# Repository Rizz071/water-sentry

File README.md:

# WaterSentry 🌊🏹

**WaterSentry** — это полностью автономная система дальнего беспроводного мониторинга уровня жидкости и предотвращения затоплений. 

Проект разработан для условий, где **абсолютно недоступны или ненадежны классические каналы связи**: нет Wi-Fi, интернета, сотовых сетей (GSM) и абонентской платы. Связь между удаленным датчиком и базовой станцией осуществляется напрямую по радиоканалу LoRa.

---

## 💡 Как это работает

1. **Удаленный датчик** устанавливается в месте возможного разлива (подвал, колодец, резервуар, насосная). Раз в 5 минут он отправляет короткий сигнал «я жив» (*heartbeat*).
2. **В случае перелива** датчик мгновенно выходит из режима ожидания и отправляет внеочередной пакет с флагом аварии.
3. **Базовая станция**, находящаяся на значительном удалении (в доме, диспетчерской), принимает сигнал, включает световую индикацию тревоги и запускает мощную сирену (зуммер) для привлечения внимания человека.

---

## 🚀 Ключевые особенности

* **Независимость от инфраструктуры:** Никаких сим-карт, роутеров и облачных сервисов. Прямая связь «точка-точка».
* **Огромная дальность:** Благодаря модулям LoRa на частоте 433 МГц сигнал уверенно пробивает железобетонные перекрытия, стены и распространяется на большие расстояния в условиях сложного рельефа.
* **Экстремальный минимализм протокола:** Данные упакованы в компактную структуру размером всего **6 байт**. Это минимизирует время работы передатчика в эфире (*Time on Air*), повышает пробивную способность радиосигнала и экономит энергию.
* **Промышленная надежность:** Код написан на **чистом Си** под нативный фреймворк **ESP-IDF v5.x**.
* **Гибкая отладка

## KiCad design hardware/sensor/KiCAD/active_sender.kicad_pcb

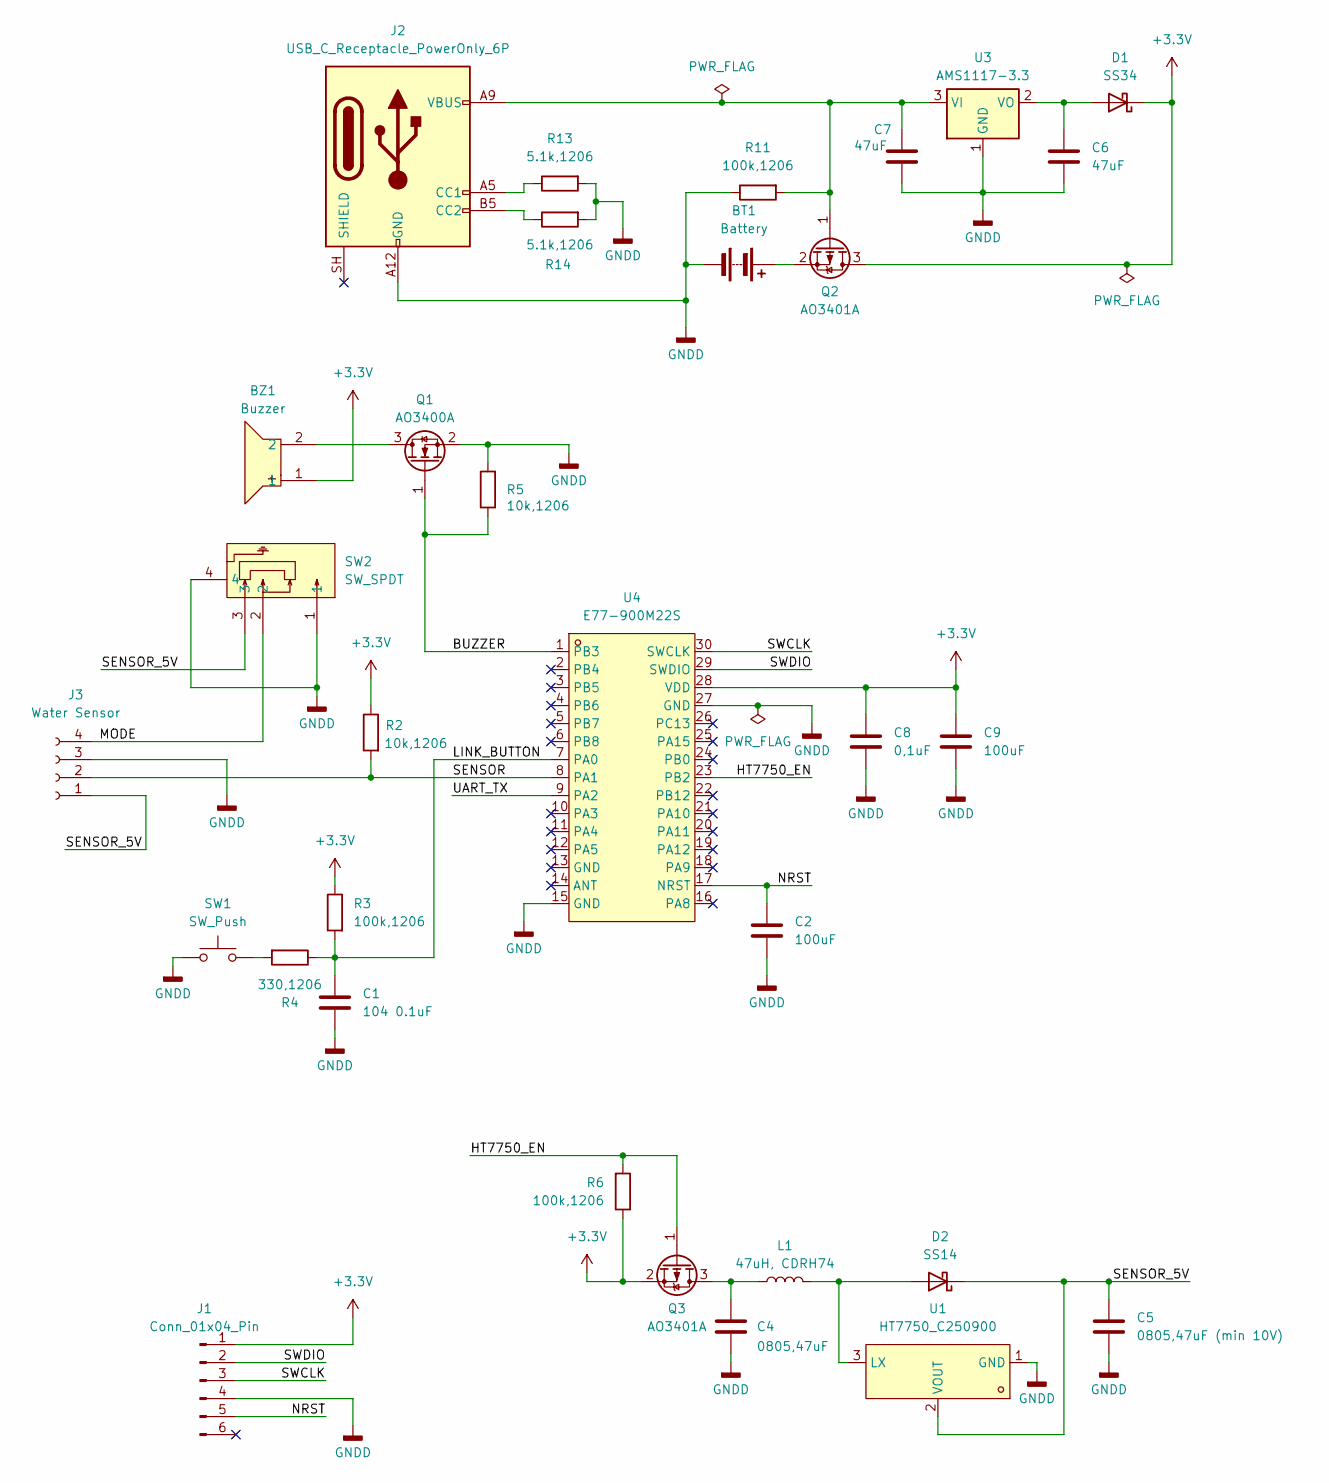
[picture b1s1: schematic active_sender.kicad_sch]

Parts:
BT1: Battery; CR123A-SMD_BH-123A-B5BA003
BZ1: Buzzer; Huaneng MLT-9650; MPN MLT-9650; LCSC Part C96127
C1: 104 0.1uF; C_0805_2012Metric_Pad1.18x1.45mm_HandSolder
C2, C9: 100uF; C_0805_2012Metric_Pad1.18x1.45mm_HandSolder
C4: 0805,47uF; C_0805_2012Metric_Pad1.18x1.45mm_HandSolder
C5: 0805,47uF (min 10V); C_0805_2012Metric_Pad1.18x1.45mm_HandSolder
C6, C7: 47uF; C_0805_2012Metric_Pad1.18x1.45mm_HandSolder
C8: 0,1uF; C_0805_2012Metric_Pad1.18x1.45mm_HandSolder
D1: SS34; D_SMA
D2: SS14; D_SMA
J1: Conn_01x04_Pin; PinHeader_2x03_P2.54mm_Vertical_SMD
J2: USB_C_Receptacle_PowerOnly_6P; USB_C_Receptacle_GCT_USB4125-xx-x-0190_6P_TopMnt_Horizontal
J3: Water Sensor; JST_XH_S4B-XH-SM4-TB_1x04-1MP_P2.50mm_Horizontal
L1: 47uH, CDRH74; L_7.3x7.3_H4.5
Q1: AO3400A; SOT-23
Q2, Q3: AO3401A; SOT-23
R2, R5: 10k,1206; R_1206_3216Metric_Pad1.30x1.75mm_HandSolder
R3, R6, R11: 100k,1206; R_1206_3216Metric_Pad1.30x1.75mm_HandSolder
R4: 330,1206; R_1206_3216Metric_Pad1.30x1.75mm_HandSolder
R13, R14: 5.1k,1206; R_1206_3216Metric_Pad1.30x1.75mm_HandSolder
SW1: SW_Push; SW_Push_1TS009xxxx-xxxx-xxxx_6x6x5mm
SW2: SW_SPDT; MSK12-C02; MPN MSK12C02; LCSC Part C431540
U1: HT7750_C250900; HT7750; MPN HT7750; LCSC Part C250900
U3: AMS1117-3.3; SOT-223-3_TabPin2
U4: E77-900M22S; COMM-SMD_30P-L20.0-W14.0-P1.27; MPN E77-900M22S; LCSC Part C5124422

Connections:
+3.3V: BZ1.1, C8.1, C9.1, D1.1 (K), J1.1, Q2.3 (D), Q3.2 (S), R2.1, R3.1, R6.1, U4.28 (VDD)
/BUZZER: Q1.1 (G), R5.1, U4.1 (PB3)
/HT7750_EN: Q3.1 (G), R6.2, U4.23 (PB2)
/LINK_BUTTON: C1.1, R3.2, R4.1, U4.7 (PA0)
/MODE: J3.4, SW2.2
/NRST: C2.1, J1.5, U4.17 (NRST)
/SENSOR: J3.2, R2.2, U4.8 (PA1)
/SENSOR_5V: C5.1, D2.1 (K), J3.1, SW2.3, U1.2 (VOUT)
/SWCLK: J1.3, U4.30 (SWCLK)
/SWDIO: J1.2, U4.29 (SWDIO)
/UART_TX: U4.9 (PA2)
GNDD: BT1.2 (-), C1.2, C2.2, C4.2, C5.2, C6.2, C7.2, C8.2, C9.2, J1.4, J2.A12 (GND), J2.B12 (GND), J3.3, Q1.2 (S), R5.2, R11.1, R13.2, R14.2, SW1.1, SW2.1, SW2.4, U1.1 (GND), U3.1 (GND), U4.15 (GND), U4.27 (GND)
unnamed: BT1.1 (+), Q2.2 (S)
unnamed: C6.1, D1.2 (A), U3.2 (VO)
unnamed: D2.2 (A), L1.2, U1.3 (LX)
unnamed: J2.A5 (CC1), R13.1
unnamed: J2.B5 (CC2), R14.1
unnamed: BZ1.2, Q1.3 (D)
unnamed: C7.1, J2.A9 (VBUS), J2.B9 (VBUS), Q2.1 (G), R11.2, U3.3 (VI)
unnamed: C4.1, L1.1, Q3.3 (D)
unnamed: R4.2, SW1.2

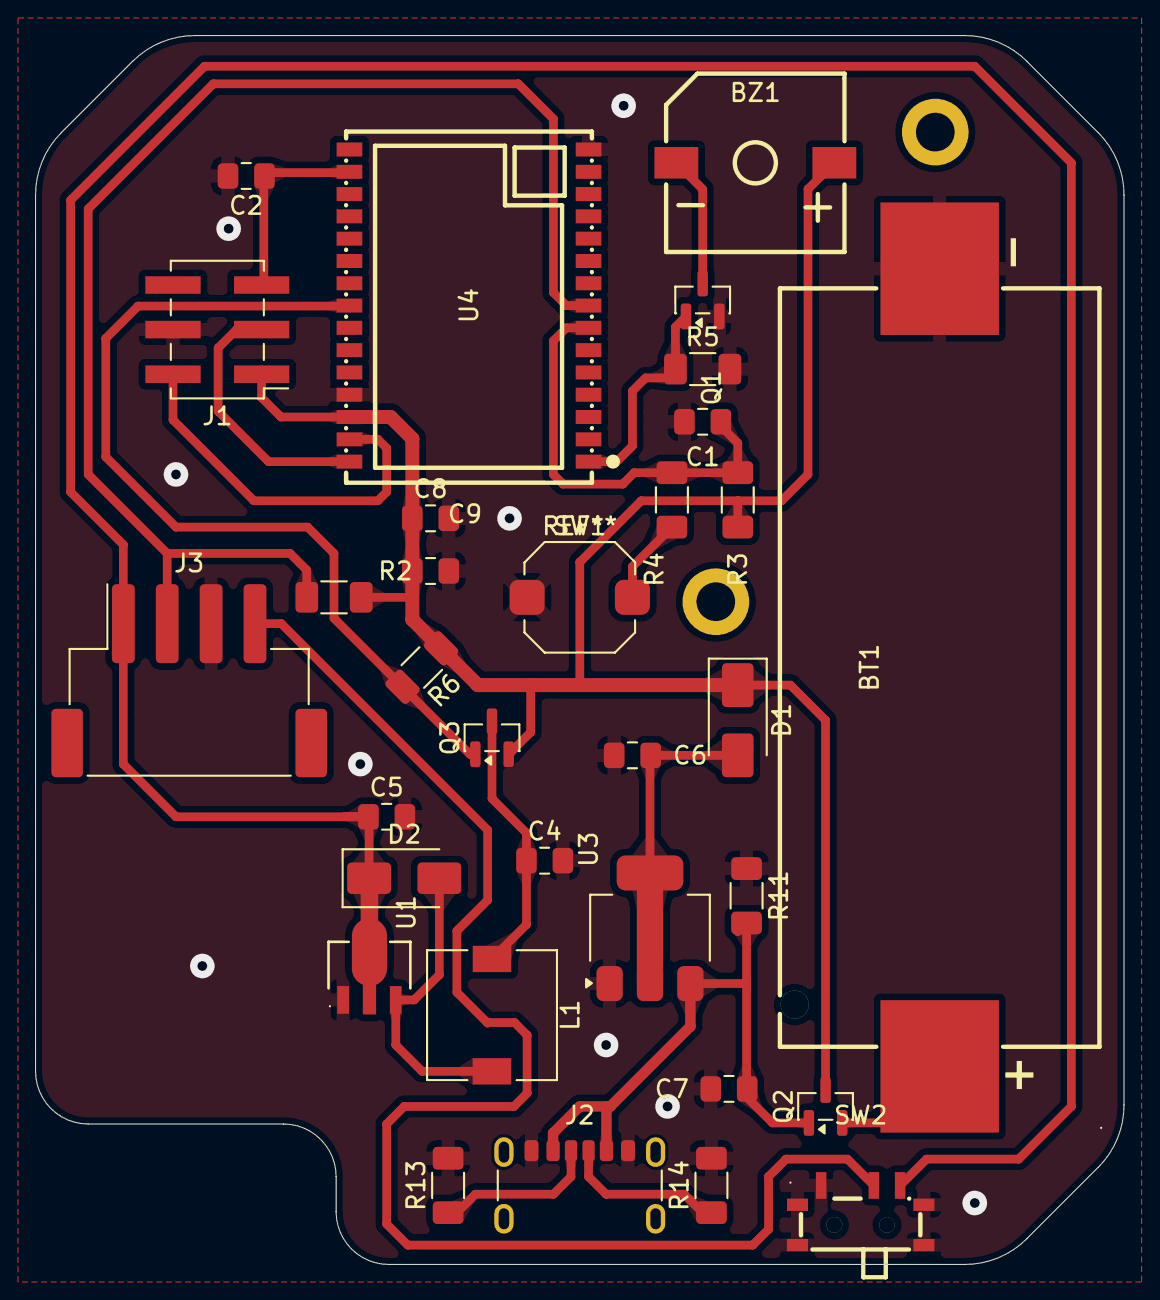
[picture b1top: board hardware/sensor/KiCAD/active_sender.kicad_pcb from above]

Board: 2 copper layers, 62.0 x 70.0 mm, 32 parts (0 on the bottom side), 20 nets.

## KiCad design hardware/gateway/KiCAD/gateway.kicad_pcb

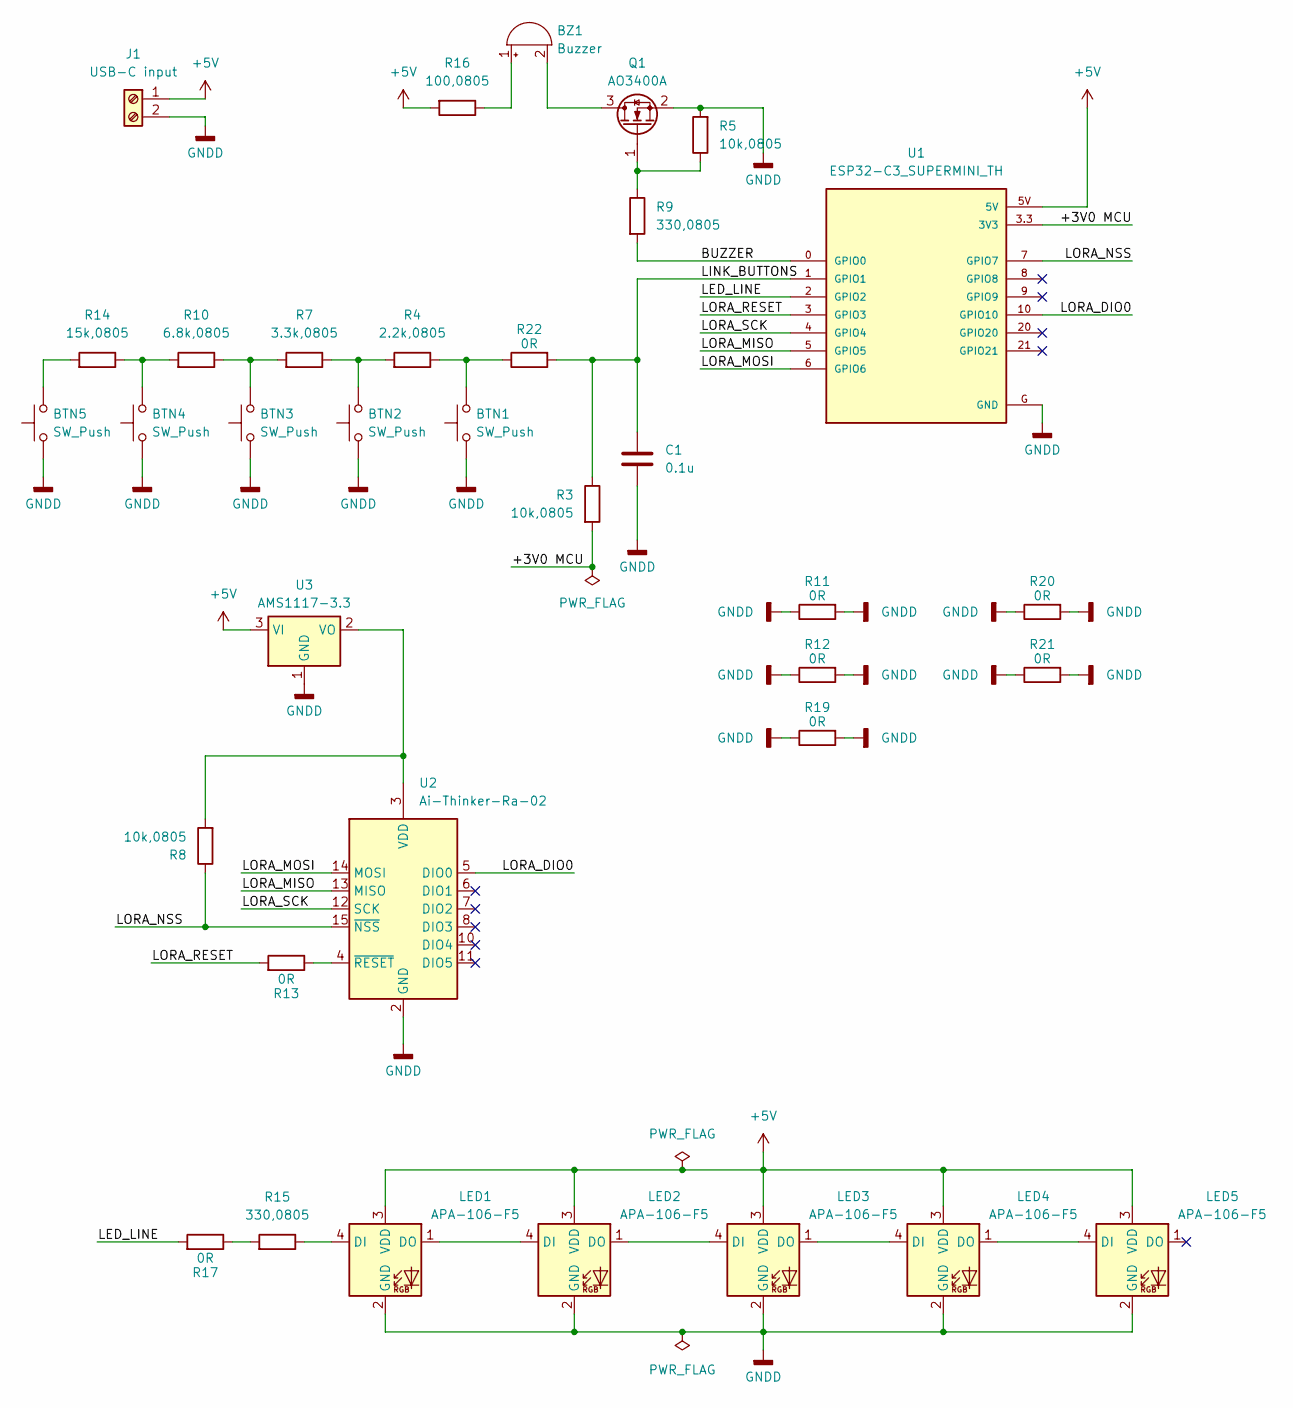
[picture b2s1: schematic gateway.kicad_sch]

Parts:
BTN1, BTN2, BTN3, BTN4, BTN5: SW_Push; SW_PUSH_6mm_H5mm
BZ1: Buzzer; Buzzer_12x9.5RM7.6
C1: 0.1u; C_0805_2012Metric_Pad1.18x1.45mm_HandSolder
J1: USB-C input; TerminalBlock_Phoenix_MKDS-1,5-2_1x02_P5.00mm_Horizontal
LED1, LED2, LED3, LED4, LED5: APA-106-F5; LED_D5.0mm-4_RGB_Staggered_Pins
Q1: AO3400A; SOT-23
R3, R5, R8: 10k,0805; R_0805_2012Metric_Pad1.20x1.40mm_HandSolder
R4: 2.2k,0805; R_0805_2012Metric_Pad1.20x1.40mm_HandSolder
R7: 3.3k,0805; R_0805_2012Metric_Pad1.20x1.40mm_HandSolder
R9, R15: 330,0805; R_0805_2012Metric_Pad1.20x1.40mm_HandSolder
R10: 6.8k,0805; R_0805_2012Metric_Pad1.20x1.40mm_HandSolder
R11, R12, R13, R17, R19, R20, R21, R22: 0R; R_2512_6332Metric_Pad1.40x3.35mm_HandSolder
R14: 15k,0805; R_0805_2012Metric_Pad1.20x1.40mm_HandSolder
R16: 100,0805; R_0805_2012Metric_Pad1.20x1.40mm_HandSolder
U1: ESP32-C3_SUPERMINI_TH; MODULE_ESP32-C3_SUPERMINI_TH
U2: Ai-Thinker-Ra-02; Ai-Thinker-Ra-01-LoRa BREAKOUT BOARD
U3: AMS1117-3.3; SOT-223-3_TabPin2

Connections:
+5V: J1.1, LED1.3 (VDD), LED2.3 (VDD), LED3.3 (VDD), LED4.3 (VDD), LED5.3 (VDD), R16.2, U1.5V, U3.3 (VI)
/+3V0 MCU: R3.2, U1.3.3 (3V3)
/BUZZER: R9.2, U1.0 (GPIO0)
/LED_LINE: R17.2, U1.2 (GPIO2)
/LINK_BUTTONS: C1.1, R3.1, R22.2, U1.1 (GPIO1)
/LORA_DIO0: U1.10 (GPIO10), U2.5 (DIO0)
/LORA_MISO: U1.5 (GPIO5), U2.13 (MISO)
/LORA_MOSI: U1.6 (GPIO6), U2.14 (MOSI)
/LORA_NSS: R8.1, U1.7 (GPIO7), U2.15 (~NSS)
/LORA_RESET: R13.2, U1.3 (GPIO3)
/LORA_SCK: U1.4 (GPIO4), U2.12 (SCK)
GNDD: BTN1.1, BTN2.1, BTN3.1, BTN4.1, BTN5.1, C1.2, J1.2, LED1.2 (GND), LED2.2 (GND), LED3.2 (GND), LED4.2 (GND), LED5.2 (GND), Q1.2 (S), R5.2, R11.1, R11.2, R12.1, R12.2, R19.1, R19.2, R20.1, R20.2, R21.1, R21.2, U1.G (GND), U2.1 (GND), U2.2 (GND), U2.9 (GND), U2.16 (GND), U3.1 (GND)
unnamed: BTN1.2, R4.1, R22.1
unnamed: BTN2.2, R4.2, R7.1
unnamed: BTN3.2, R7.2, R10.1
unnamed: BTN4.2, R10.2, R14.1
unnamed: BTN5.2, R14.2
unnamed: BZ1.1 (+), R16.1
unnamed: BZ1.2 (-), Q1.3 (D)
unnamed: LED1.4 (DI), R15.1
unnamed: LED1.1 (DO), LED2.4 (DI)
unnamed: LED2.1 (DO), LED3.4 (DI)
unnamed: LED3.1 (DO), LED4.4 (DI)
unnamed: LED4.1 (DO), LED5.4 (DI)
unnamed: Q1.1 (G), R5.1, R9.1
unnamed: R15.2, R17.1
unnamed: R8.2, U2.3 (VDD), U3.2 (VO)
unnamed: R13.1, U2.4 (~RESET)

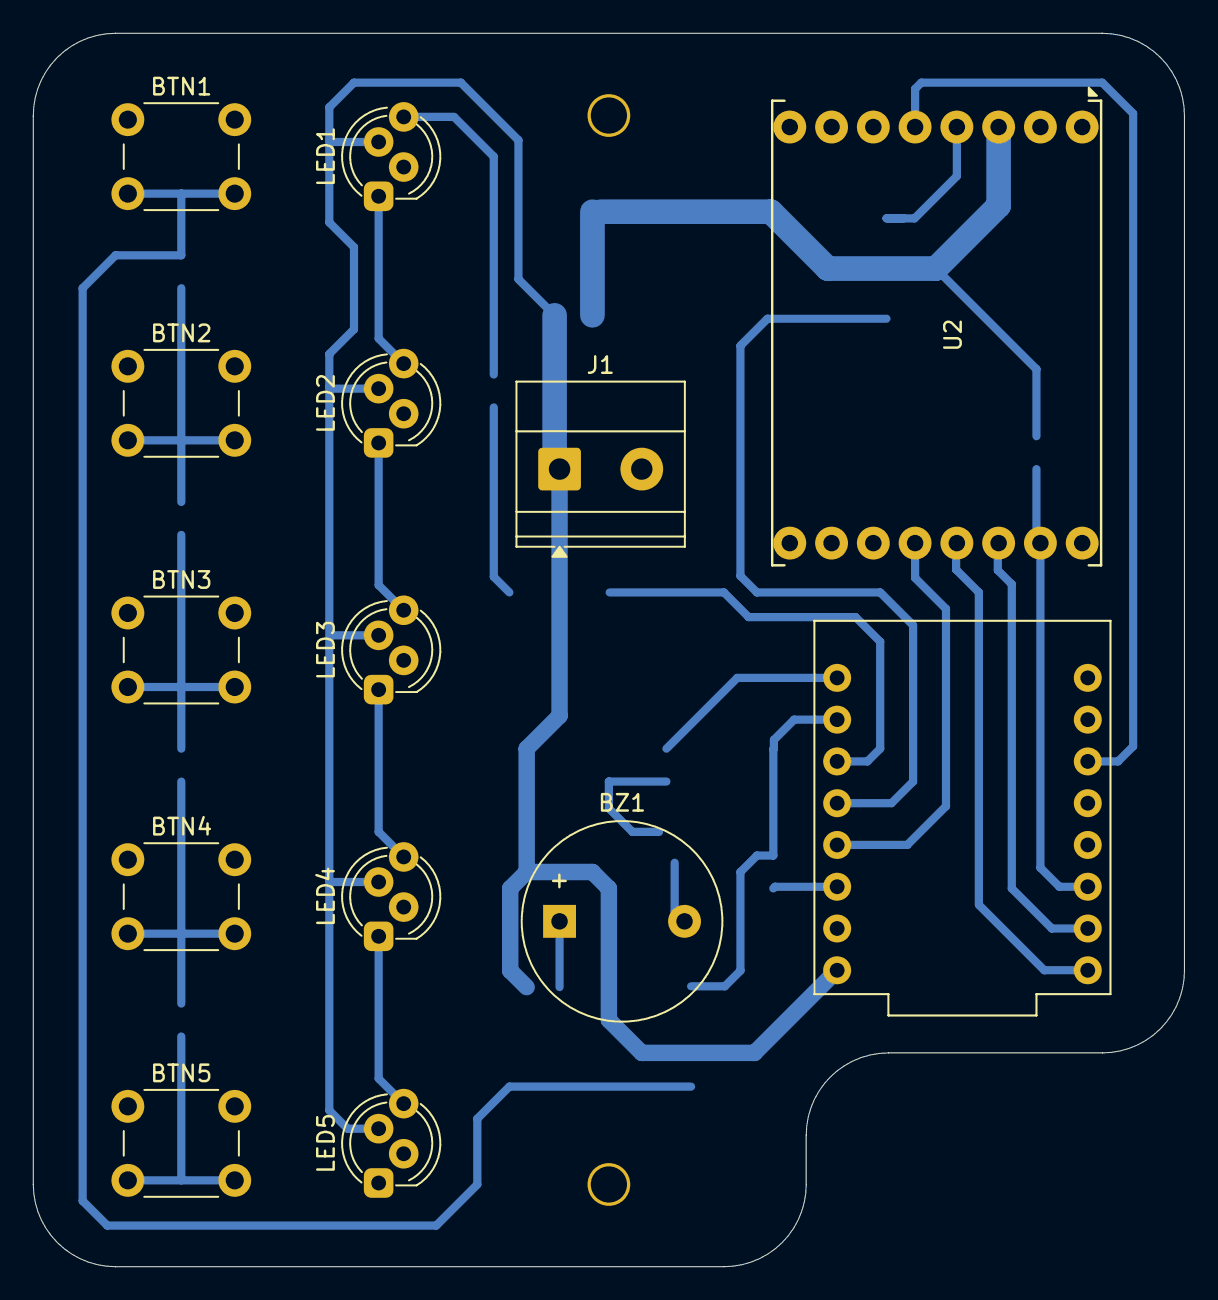
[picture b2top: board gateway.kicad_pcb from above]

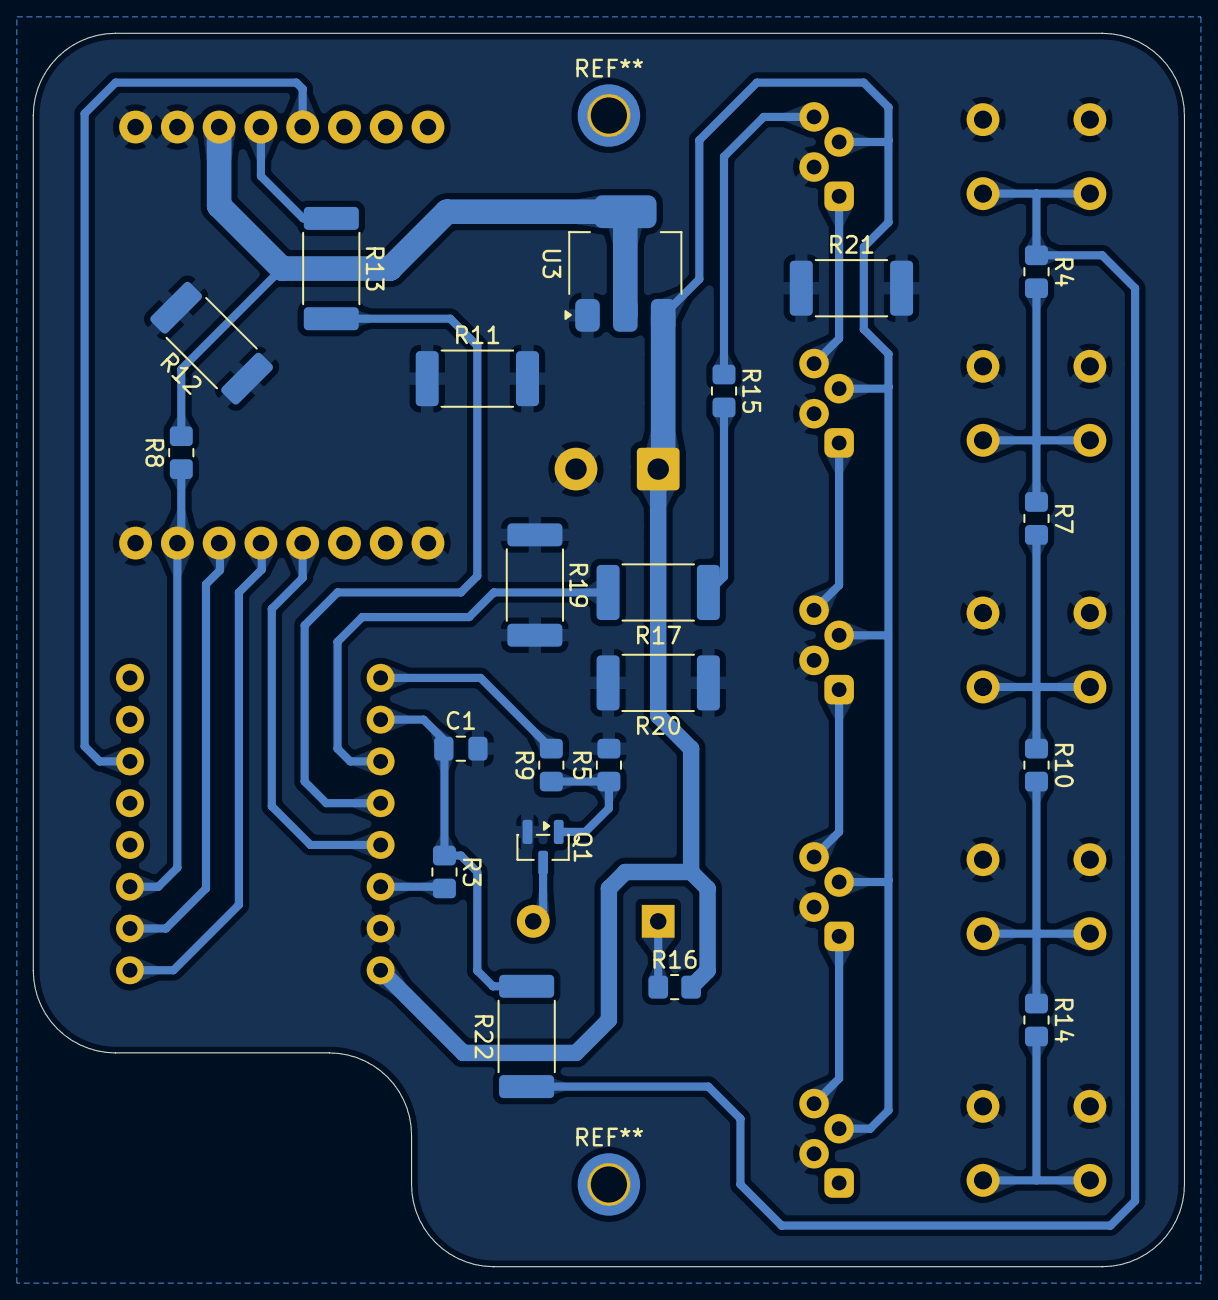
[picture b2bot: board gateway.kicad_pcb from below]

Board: 2 copper layers, 70.0 x 75.0 mm, 35 parts (21 on the bottom side), 28 nets.

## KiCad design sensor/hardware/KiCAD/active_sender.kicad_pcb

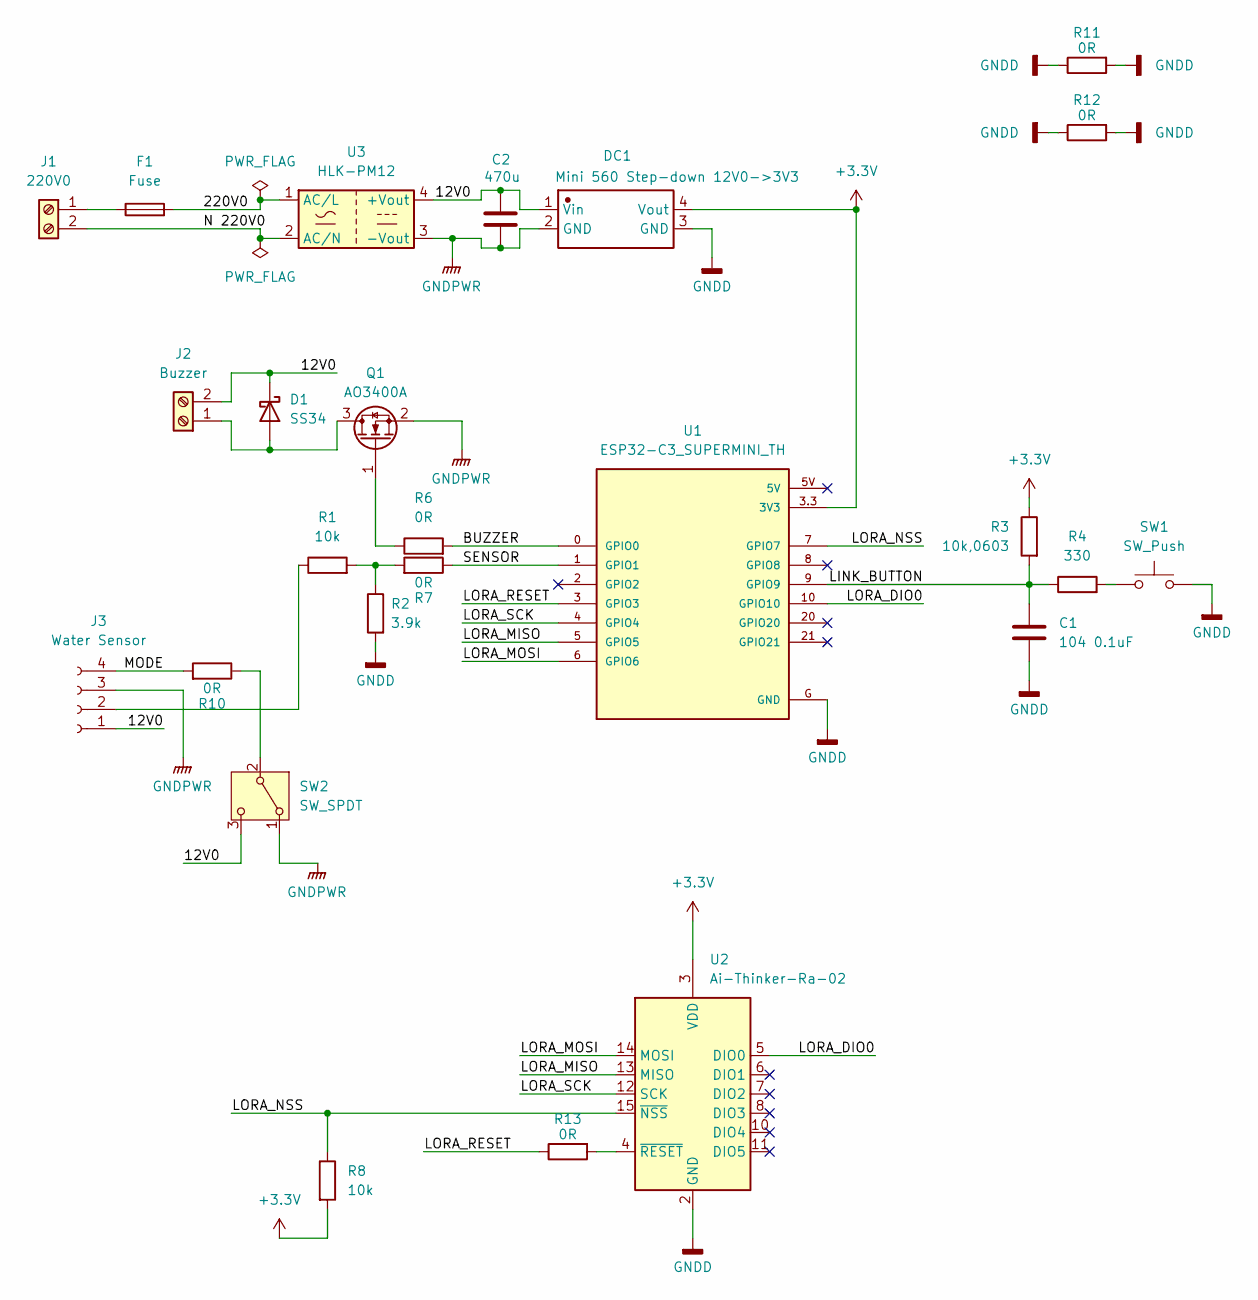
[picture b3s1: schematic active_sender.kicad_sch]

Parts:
C1: 104 0.1uF; C_0805_2012Metric_Pad1.18x1.45mm_HandSolder
C2: 470u; C_Radial_D8.0mm_H11.5mm_P3.50mm
D1: SS34; D_SMA
DC1: Mini 560 Step-down 12V0->3V3; MINI 560 PRO
F1: Fuse; Fuseholder_Cylinder-5x20mm_Schurter_0031_8201_Horizontal_Op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
J1: 220V0; TerminalBlock_Phoenix_MKDS-1,5-2_1x02_P5.00mm_Horizontal
J2: Buzzer; TerminalBlock_Phoenix_MKDS-1,5-2_1x02_P5.00mm_Horizontal
J3: Water Sensor; JST_XH_S4B-XH-A-1_1x04_P2.50mm_Horizontal
Q1: AO3400A; SOT-23
R1, R8: 10k; R_1206_3216Metric_Pad1.30x1.75mm_HandSolder
R2: 3.9k; R_1206_3216Metric_Pad1.30x1.75mm_HandSolder
R3: 10k,0603; R_1206_3216Metric_Pad1.30x1.75mm_HandSolder
R4: 330; R_1206_3216Metric_Pad1.30x1.75mm_HandSolder
R6, R7, R10, R11, R12, R13: 0R; R_2512_6332Metric_Pad1.40x3.35mm_HandSolder
SW1: SW_Push; SW_PUSH_6mm_H5mm
SW2: SW_SPDT; SS12D00
U1: ESP32-C3_SUPERMINI_TH; MODULE_ESP32-C3_SUPERMINI_TH
U2: Ai-Thinker-Ra-02; Ai-Thinker-Ra-01-LoRa BREAKOUT BOARD
U3: HLK-PM12; Converter_ACDC_Hi-Link_HLK-PMxx

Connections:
+3.3V: DC1.4 (Vout), R3.1, R8.2, U1.3.3 (3V3), U2.3 (VDD)
/12V0: C2.1, D1.1 (K), DC1.1 (Vin), J2.2, J3.1, SW2.3 (C), U3.4 (+Vout)
/220V0: F1.2, U3.1 (AC/L)
/BUZZER: R6.2, U1.0 (GPIO0)
/LINK_BUTTON: C1.1, R3.2, R4.1, U1.9 (GPIO9)
/LORA_DIO0: U1.10 (GPIO10), U2.5 (DIO0)
/LORA_MISO: U1.5 (GPIO5), U2.13 (MISO)
/LORA_MOSI: U1.6 (GPIO6), U2.14 (MOSI)
/LORA_NSS: R8.1, U1.7 (GPIO7), U2.15 (~NSS)
/LORA_RESET: R13.1, U1.3 (GPIO3)
/LORA_SCK: U1.4 (GPIO4), U2.12 (SCK)
/MODE: J3.4, R10.2
/N 220V0: J1.2, U3.2 (AC/N)
/SENSOR: R7.1, U1.1 (GPIO1)
GNDD: C1.2, DC1.3 (GND), R2.2, R11.1, R11.2, R12.1, R12.2, SW1.2, U1.G (GND), U2.1 (GND), U2.2 (GND), U2.9 (GND), U2.16 (GND)
GNDPWR: C2.2, DC1.2 (GND), J3.3, Q1.2 (S), SW2.1 (A), U3.3 (-Vout)
unnamed: D1.2 (A), J2.1, Q1.3 (D)
unnamed: F1.1, J1.1
unnamed: J3.2, R1.1
unnamed: Q1.1 (G), R6.1
unnamed: R1.2, R2.1, R7.2
unnamed: R4.2, SW1.1
unnamed: R10.1, SW2.2 (B)
unnamed: R13.2, U2.4 (~RESET)

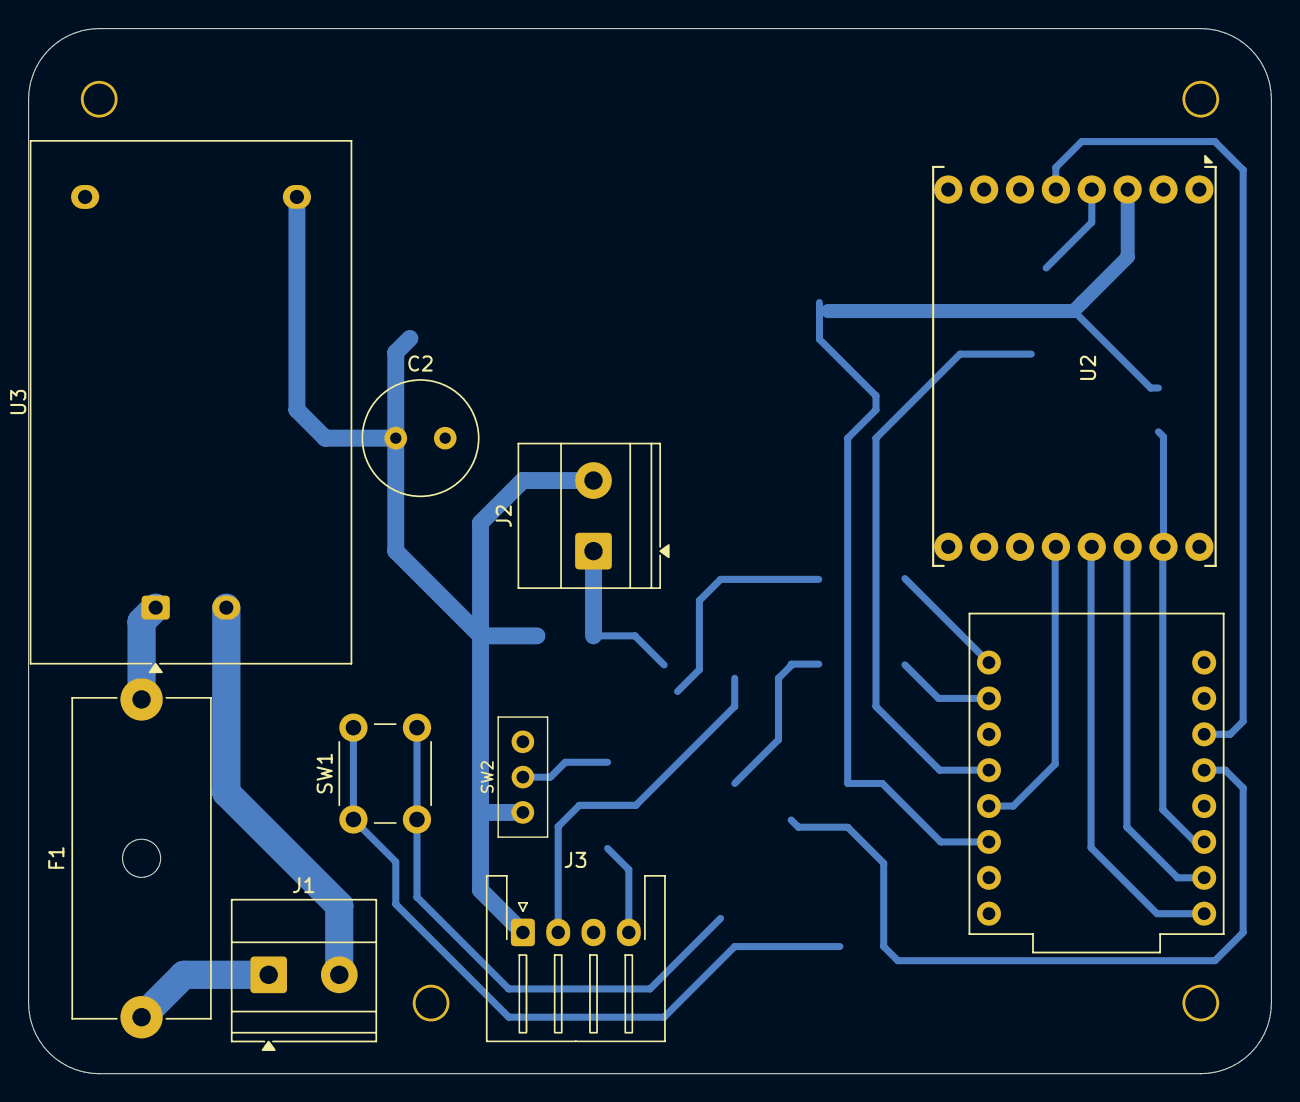
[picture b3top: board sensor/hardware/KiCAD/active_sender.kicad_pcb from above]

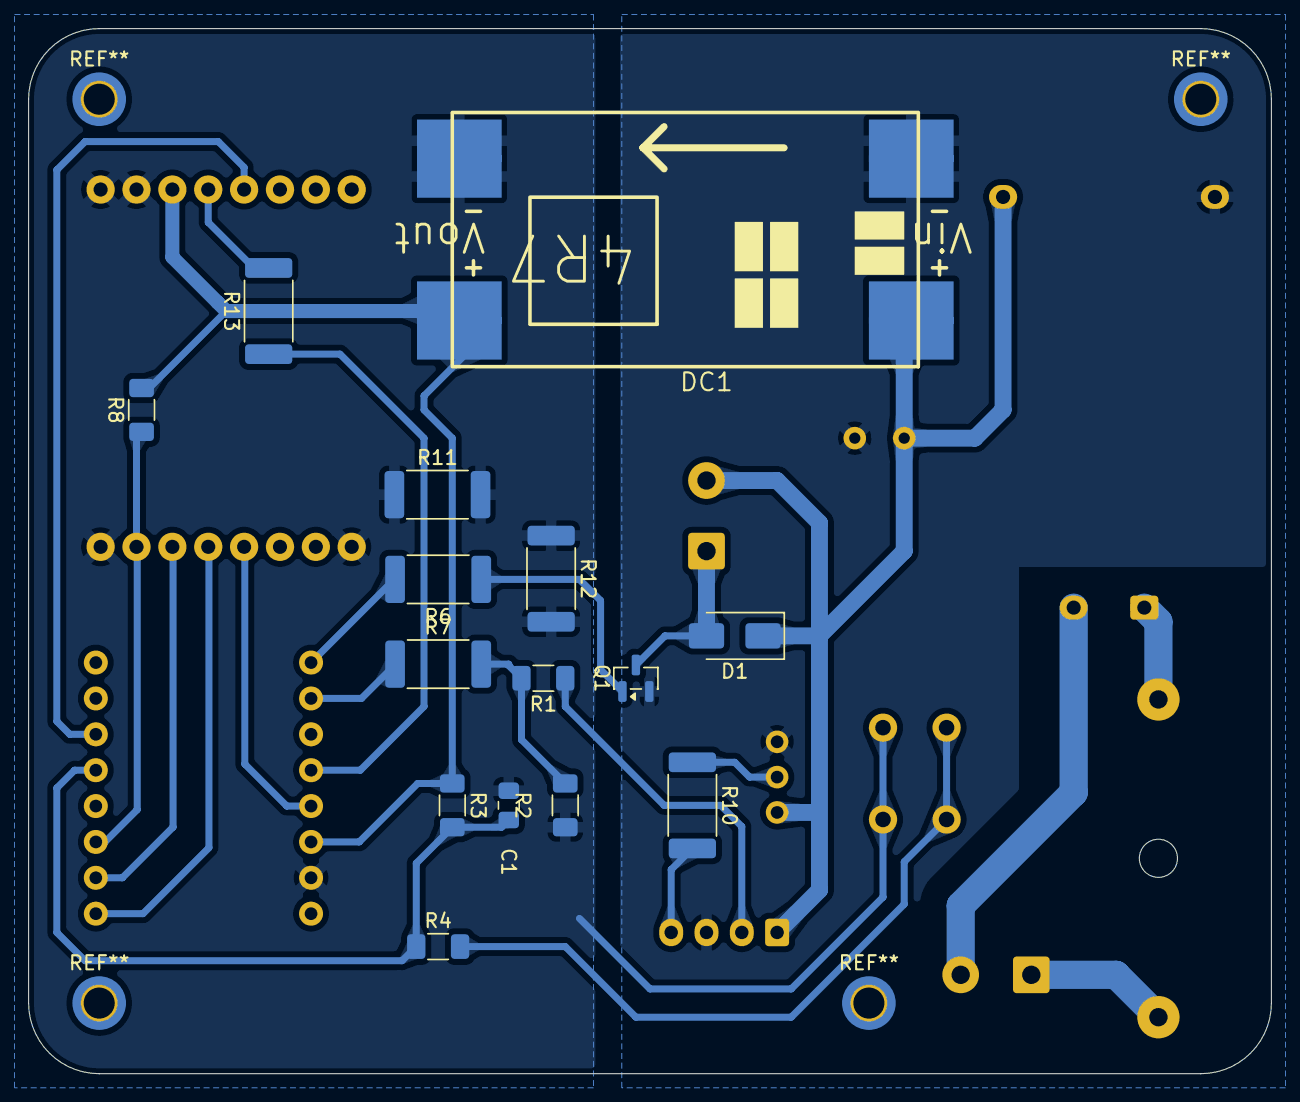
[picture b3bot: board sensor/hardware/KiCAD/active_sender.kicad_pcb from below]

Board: 2 copper layers, 88.0 x 74.0 mm, 25 parts (15 on the bottom side), 24 nets.

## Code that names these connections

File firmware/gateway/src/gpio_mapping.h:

#ifndef GPIO_MAPPING_H
#define GPIO_MAPPING_H


#define BUZZER_PIN GPIO_NUM_0
#define LED_LINE_PIN GPIO_NUM_2
#define LINK_BUTTONS_PIN GPIO_NUM_1




#endif // GPIO_MAPPING_H

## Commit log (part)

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2026-06-25 all: init
2026-06-25 all: README.md
